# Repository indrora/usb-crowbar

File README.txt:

...    ::: .::::::. :::::::.          .,-::::: :::::::..       ...    .::    .   .::::::::::.    :::.    :::::::..   
 ;;     ;;;;;;`    `  ;;;'';;'       ,;;;'````' ;;;;``;;;;   .;;;;;;;. ';;,  ;;  ;;;'  ;;;'';;'   ;;`;;   ;;;;``;;;;  
[['     [[['[==/[[[[, [[[__[[\.      [[[         [[[,/[[['  ,[[     \[[,'[[, [[, [['   [[[__[[\. ,[[ '[[,  [[[,/[[['  
$$      $$$  '''    $ $$""""Y$$ cccc $$$         $$$$$$c    $$$,     $$$  Y$c$$$c$P    $$""""Y$$c$$$cc$$$c $$$$$$c    
88    .d888 88b    dP_88o,,od8P      `88bo,__,o, 888b "88bo,"888,_ _,88P   "88"888    _88o,,od8P 888   888,888b "88bo,
 "YmmMMMM""  "YMmMY" ""YUMMMP"         "YUMMMMMP"MMMM   "W"   "YMMMMMP"     "M "M"    ""YUMMMP"  YMM   ""` MMMM   "W" 

The USB Crowbar is a footprint replacement for the venerable USB-B full size connector. 

The vast majority of right-angle board-mount USB Type B connectors have the same footprint, down to the shape
and size of the pads, body, etc. 

A friend of mine was tired of the USB connectors failing on her DJ equipment after just a few years. Sometimes,
that was just a few shows over a few months. 

Skill issue on my part, I said the words "This should be easy".

Reader: it was not easy.

You can buy these in sticks of five from my Tindie store: https://www.tindie.com/products/indrora/usb-crowbar/

--- DETAILED INSTALLATION INSTRUCTIONS ---

1. Verify that the USB B connector on your device is compatible: It must be right angle (that is, it plugs in
   parallel to the board surface, rather than jamming into it), and must have the angled side of the plug at
   the top ("away" from the board). Generally, it should look like what's on the Arduino Uno. Wikimedia
   has a pretty good picture of what you're looking for: https://commons.wikimedia.org/wiki/File:Arduino_Uno_005.jpg
   This is *not* compatible with vertical USB connectors like the one in this photo of a Rigol oscilloscope:
   https://commons.wikimedia.org/wiki/File:Rigol_DS1054Z_Oscilloscope_Teardown_PCB_(15354017188).jpg
   https://commons.wikimedia.org/wiki/File:Rigol_DS1054Z_Oscilloscope_Teardown_PCB_(15537475561).jpg (on the right hand side)

2. Desolder your connector. Hints:
   - Add a touch of fresh solder.
   - Remove as much solder from the shield strain relief pins as you can, then trim them flat. Heat the board
     gently with a hair dryer or hot air to help reduce heat loss.
   - In my experience, once you have the four signal pins handled, you're golden. Use whatever means you need to remove the
     connector. Sometimes, this has meant being Destructive. 

3. Using 22ga wire, solder two U-shaped loops through the top of the crowbar.
4. Line up the crowbar with the footprint of the original USB connector. Tack in place one of the structural joints on the sides.
5. Solder the thru-wires on the backside of the board
6. Trim the bottom and top sides, removing excess wire. Trim the wires on the top of the crowbar as flush as you can.

/!\ At this point, you can safely test the connection.

7. Flood the structural joints on the sides with solder. It shouldn't want to lift. 
8. Clean with alcohol and allow to dry. 

-- FREQUENTLY QUESTIONED ANSWERS --

Q: MiniB? MicroB?

I've had a *ton* of requests for this. Unfortunately, it's not in the cards. 

* The physical dimensions of a USB Type C connector are against us: It's huge!
* There's maybe 3 total layouts for USB2 Type B (two thru-hole and one surface mount) that I've found. Most others are within 0.5mm of that in some dimension, with the pinout being the exact same for thru-hole versions. 
* The USB C connector housing *happens* to be exactly the width of the USB Type B connector.

Both Mini and Micro-B have a lot of different layouts (4/5 pin variants, thru-hole and SMT, different landing pads for the shell vs. sunk holes for the shell, etc.). This hasn't stopped one intrepid friend of mine who replaced the Micro-B connector on something by using 24ga stranded core wire and very carefully bodging the required lines. If you can make the space for the connector to cram it down, Do It! 

In some cases, since the connector is on a separate board, it may well be reasonable to design a replacement board for the USB connector, as was done in the case for the PS4 Controllers. Marcus Heier has a fantastic drop-in modification for several generations of PS4 controllers that you can buy from him on Tindie: https://www.tindie.com/products/mariusheier/ps4-controller-usb-c/ -- you can see the process of installing it here: https://youtu.be/o9IACHF22yc

Q: USB Type A????

One of the inspirations for this project was Palconn's USB A compatible ports: http://palconn.net/products/?id=100

Finding them is a bit tricky...

-- LICENSE --

This work is licensed under CC-BY.

I have a dream that some day, I will be able to buy these from vendors such as Palconn and Samtec as retrofits for old designs.
If you're in that scene, hmu ;)

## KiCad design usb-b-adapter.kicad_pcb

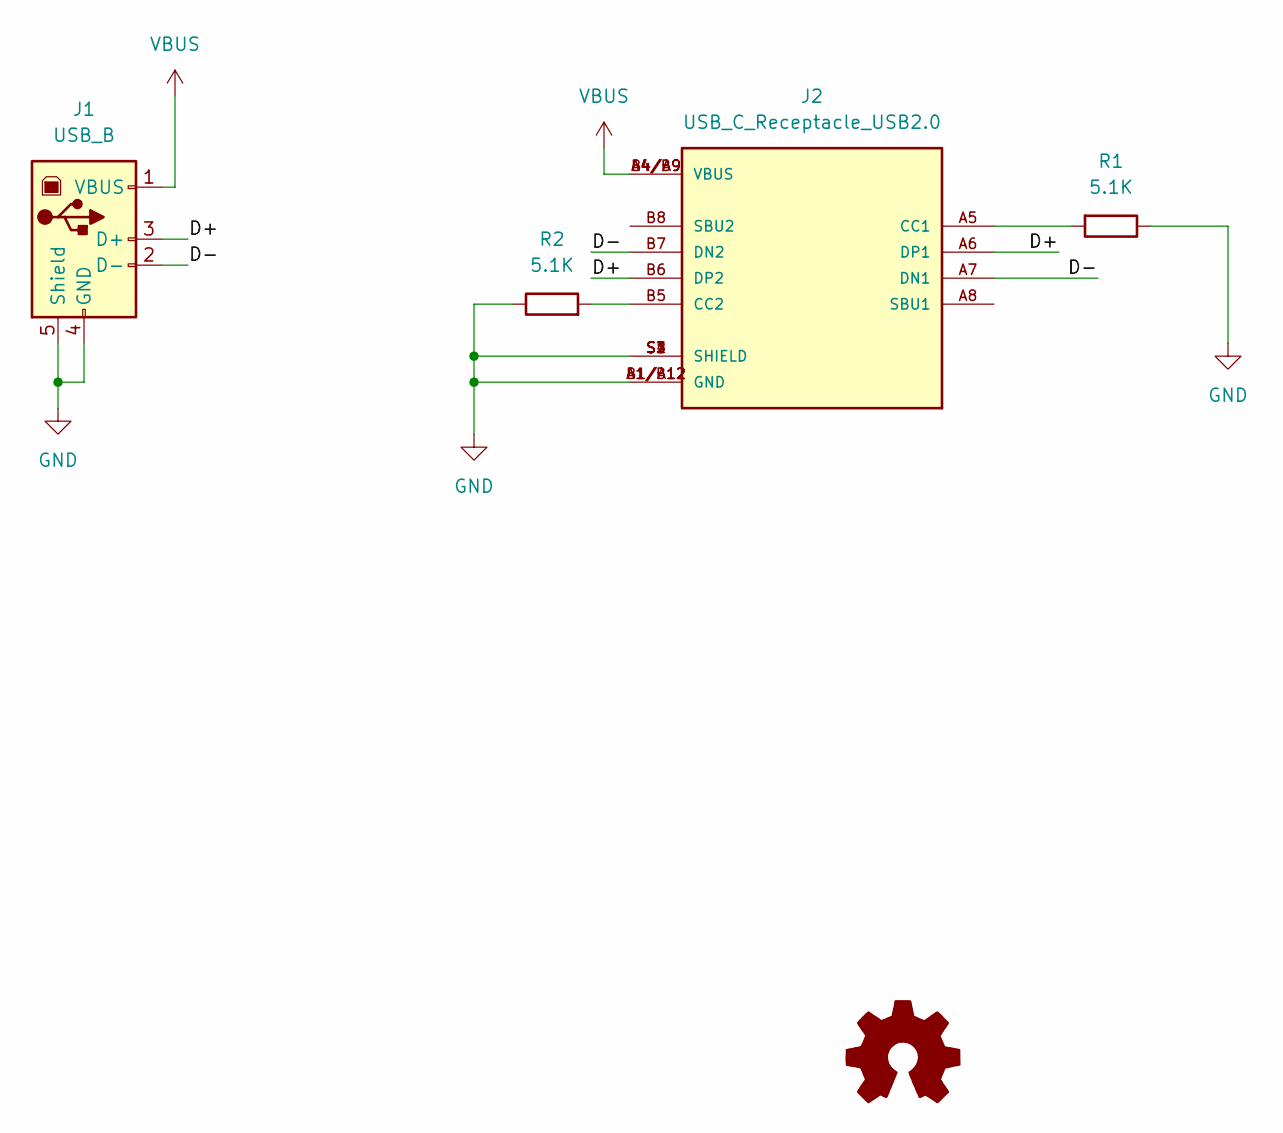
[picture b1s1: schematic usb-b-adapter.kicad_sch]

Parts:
J1: USB_B; USB_B_OST_USB-B1HSxx_Horizontal
J2: USB_C_Receptacle_USB2.0; HRO_TYPE-C-31-M-12; PARTREV 2020.12.08; LCSC C165948
R1, R2: 5.1K; R_0201_0603Metric; MPN C473460; LCSC C473460

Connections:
/D+: J1.3 (D+), J2.A6 (DP1), J2.B6 (DP2)
/D-: J1.2 (D-), J2.A7 (DN1), J2.B7 (DN2)
GND: J1.4 (GND), J1.5 (Shield), J2.A1/B12 (GND), J2.B1/A12 (GND), J2.S1 (SHIELD), J2.S2 (SHIELD), J2.S3 (SHIELD), J2.S4 (SHIELD), R1.1, R2.1
unnamed: J2.A5 (CC1), R1.2
unnamed: J2.B5 (CC2), R2.2
VBUS: J1.1 (VBUS), J2.A4/B9 (VBUS), J2.B4/A9 (VBUS)

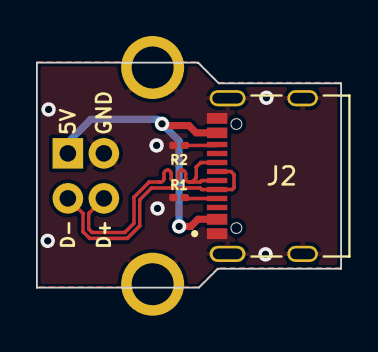
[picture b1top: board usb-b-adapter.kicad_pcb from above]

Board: 2 copper layers, 16.9 x 12.5 mm, 4 parts (0 on the bottom side), 6 nets.

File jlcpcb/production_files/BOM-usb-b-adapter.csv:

Comment,Designator,Footprint,LCSC
USB_C_Receptacle_USB2.0,J2,HRO_TYPE-C-31-M-12,C165948
5.1K,"R1,R2",R_0201_0603Metric,C473460

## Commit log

2023-10-06 Added gitignore
2023-10-06 update README with license
